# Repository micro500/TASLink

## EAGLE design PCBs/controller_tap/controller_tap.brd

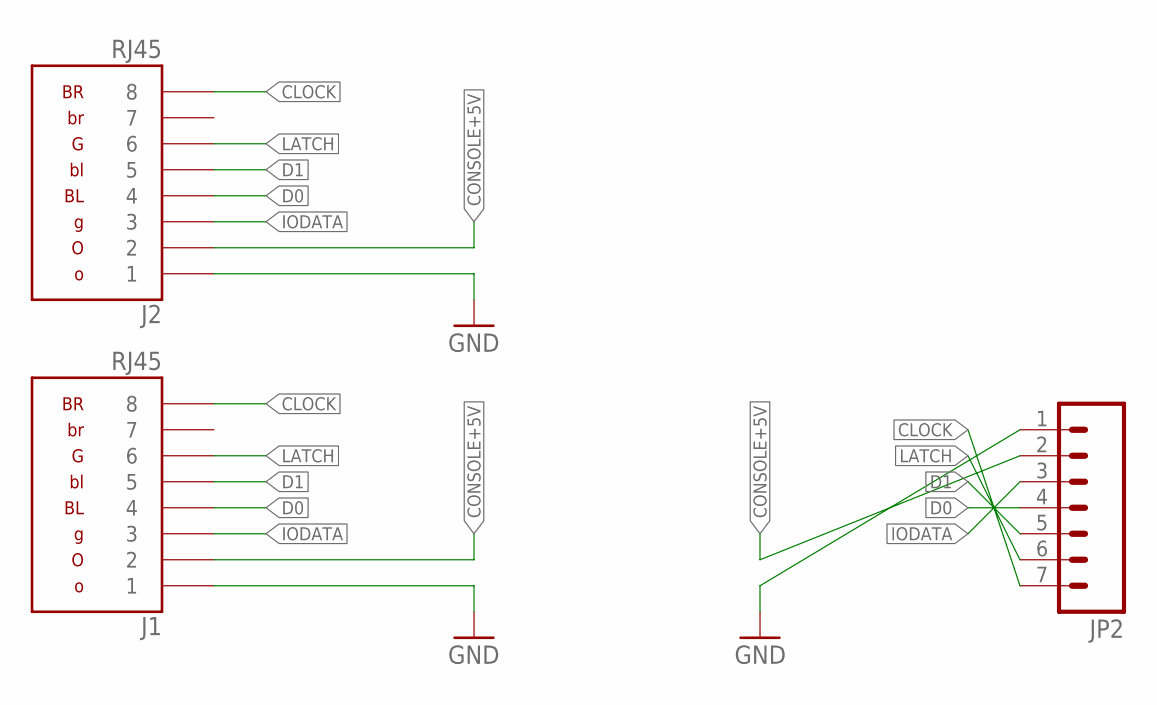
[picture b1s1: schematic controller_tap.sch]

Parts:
J1, J2: RJ45
JP2: M07; 1X07

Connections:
CLOCK: J1.8, J2.8, JP2.7
CONSOLE+5V: J1.2, J2.2, JP2.2
D0: J1.4, J2.4, JP2.4
D1: J1.5, J2.5, JP2.5
GND: J1.1, J2.1, JP2.1
IODATA: J1.3, J2.3, JP2.3
LATCH: J1.6, J2.6, JP2.6

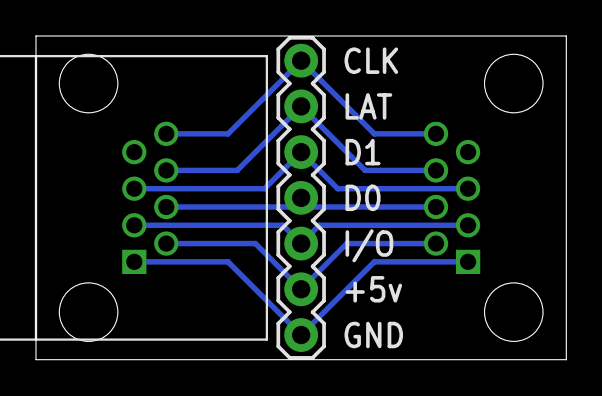
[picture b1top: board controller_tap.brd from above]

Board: 2 copper layers, 29.5 x 18.0 mm, 3 parts (1 on the bottom side), 7 nets.

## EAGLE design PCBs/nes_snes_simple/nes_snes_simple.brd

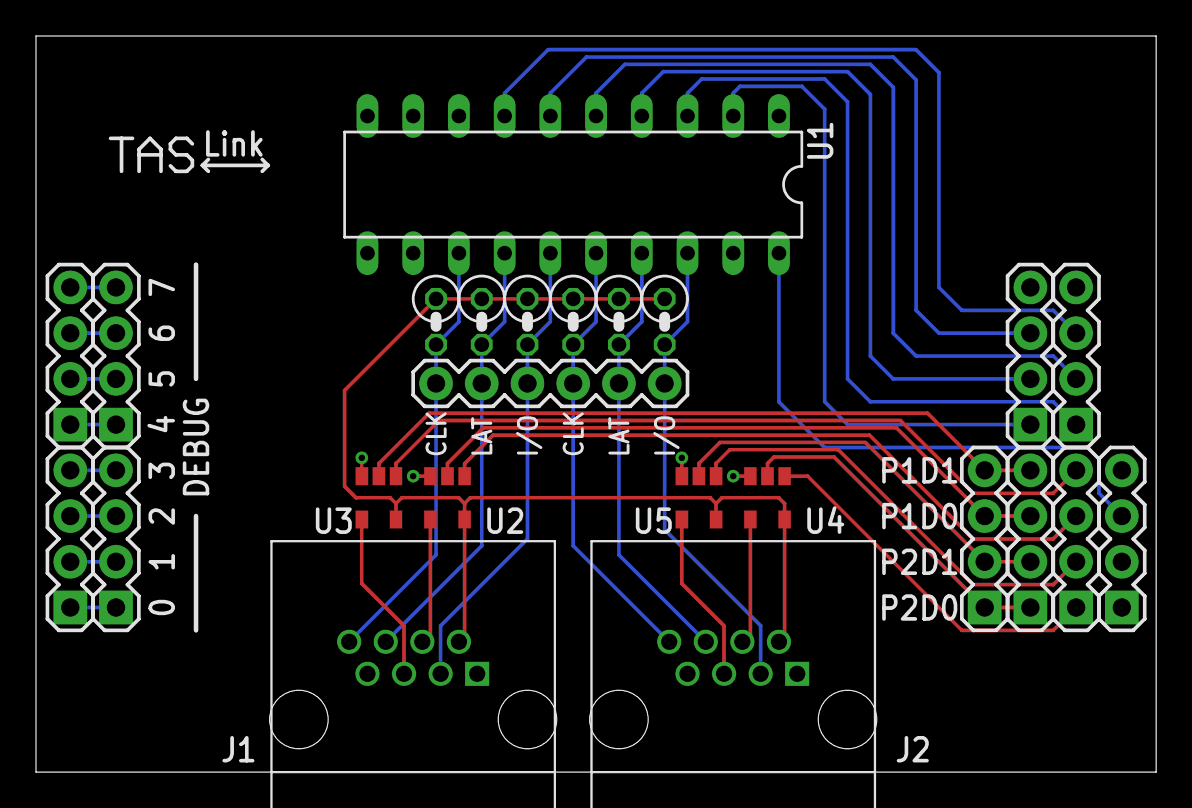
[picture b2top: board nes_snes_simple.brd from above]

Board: 2 copper layers, 62.2 x 40.9 mm, 24 parts (0 on the bottom side), 35 nets.

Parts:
J1, J2: RJ45
JP1, JP2, JP3, JP4, JP7, JP8, JP9, JP10, JP11, JP12: 1X04
JP5: 1X06
R1, R2, R3, R4, R5, R6: 3.6k; 0207/2V
U1: 74245; DIL20
U2, U3, U4, U5: MC74VHC1GT125; TSOP-5

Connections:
+3V3: JP1.3, U1.20
CONSOLE+5V: J1.2, J2.2, R1.1, R2.1, R3.1, R4.1, R5.1, R6.1, U2.P$5, U3.P$5, U4.P$5, U5.P$5
DEBUG0: JP2.4, JP9.4
DEBUG1: JP2.3, JP9.3
DEBUG2: JP2.2, JP9.2
DEBUG3: JP2.1, JP9.1
DEBUG4: JP3.4, JP10.4
DEBUG5: JP3.3, JP10.3
DEBUG6: JP3.2, JP10.2
DEBUG7: JP3.1, JP10.1
GND: J1.1, J2.1, JP1.1, U1.1, U1.10, U1.11, U1.12, U1.19, U2.P$3, U3.P$3, U4.P$3, U5.P$3
P1_CLOCK: J1.8, JP5.1, R1.2, U1.13
P1_CLOCK_LV: JP4.3, U1.7
P1_D0: J1.4, U2.P$4
P1_D0_LV: JP8.3, JP12.3, U2.P$2
P1_D0_OE_LV: JP11.3, U2.P$1
P1_D1: J1.5, U3.P$4
P1_D1_LV: JP8.4, JP12.4, U3.P$2
P1_D1_OE_LV: JP11.4, U3.P$1
P1_IODATA: J1.3, JP5.3, R5.2, U1.15
P1_IODATA_LV: JP4.2, U1.5
P1_LATCH: J1.6, JP5.2, R3.2, U1.14
P1_LATCH_LV: JP7.3, U1.6
P2_CLOCK: J2.8, JP5.4, R2.2, U1.16
P2_CLOCK_LV: JP7.2, U1.4
P2_D0: J2.4, U4.P$4
P2_D0_OE_LV: JP11.1, U4.P$1
P2_D1: J2.5, U5.P$4
P2_D1_LV: JP8.2, JP12.2, U5.P$2
P2_D1_OE_LV: JP11.2, U5.P$1
P2_DO_LV: JP8.1, JP12.1, U4.P$2
P2_IODATA: J2.3, JP5.6, R6.2, U1.18
P2_IODATA_LV: JP7.1, U1.2
P2_LATCH: J2.6, JP5.5, R4.2, U1.17
P2_LATCH_LV: JP4.1, U1.3

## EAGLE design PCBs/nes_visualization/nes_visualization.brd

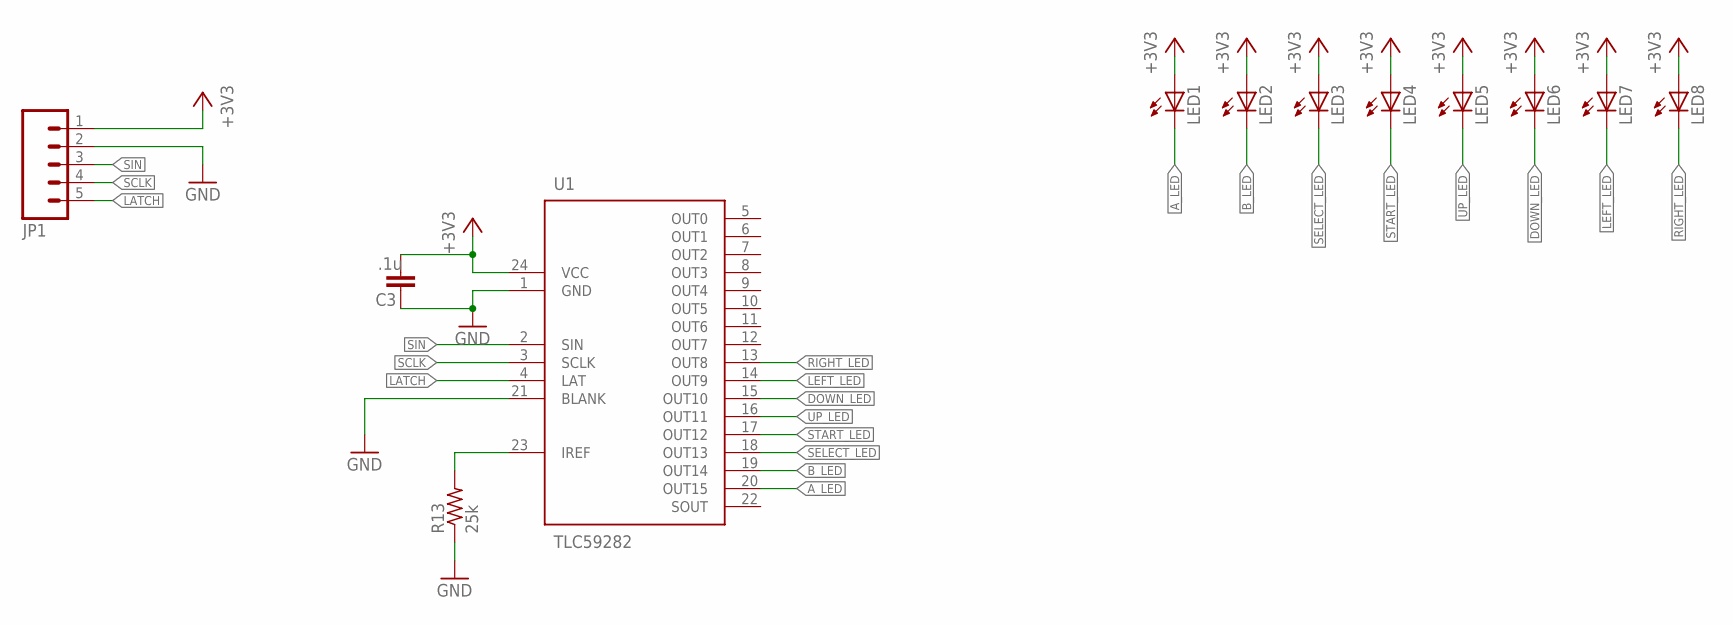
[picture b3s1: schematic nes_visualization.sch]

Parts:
C3: .1u; C0603; MOUSER# 80-C0603C104K5R
JP1: M05PTH; 1X05
LED1, LED2, LED5, LED6, LED7, LED8: LED5MM
LED3, LED4: LED3MM
R13: 25k; R0805
U1: TLC59282; R-PDSO-G24

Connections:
+3V3: C3.1, JP1.1, LED1.A, LED2.A, LED3.A, LED4.A, LED5.A, LED6.A, LED7.A, LED8.A, U1.24 (VCC)
A_LED: LED1.K (C), U1.20 (OUT15)
B_LED: LED2.K (C), U1.19 (OUT14)
DOWN_LED: LED6.K (C), U1.15 (OUT10)
GND: C3.2, JP1.2, R13.1, U1.1 (GND), U1.21 (BLANK)
LATCH: JP1.5, U1.4 (LAT)
LEFT_LED: LED7.K (C), U1.14 (OUT9)
unnamed: R13.2, U1.23 (IREF)
RIGHT_LED: LED8.K (C), U1.13 (OUT8)
SCLK: JP1.4, U1.3 (SCLK)
SELECT_LED: LED3.K (C), U1.18 (OUT13)
SIN: JP1.3, U1.2 (SIN)
START_LED: LED4.K (C), U1.17 (OUT12)
UP_LED: LED5.K (C), U1.16 (OUT11)

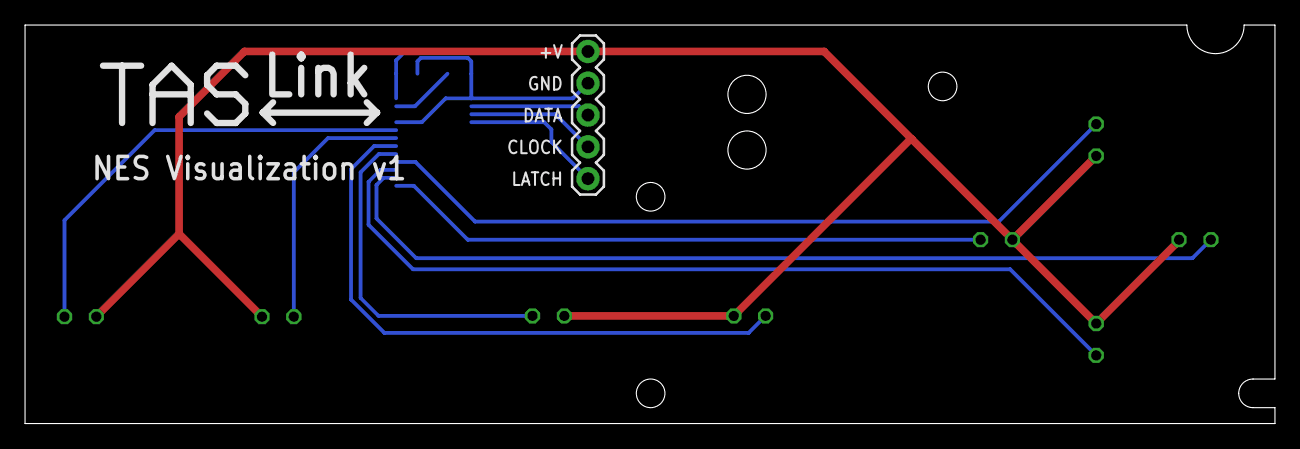
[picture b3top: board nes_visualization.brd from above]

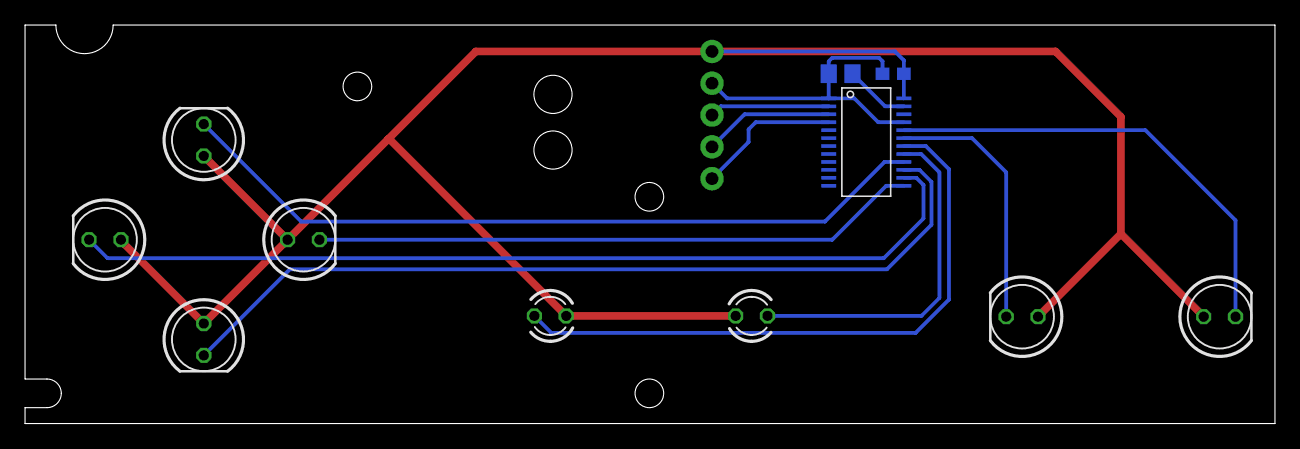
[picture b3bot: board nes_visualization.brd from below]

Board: 2 copper layers, 99.8 x 31.8 mm, 12 parts (11 on the bottom side), 14 nets.

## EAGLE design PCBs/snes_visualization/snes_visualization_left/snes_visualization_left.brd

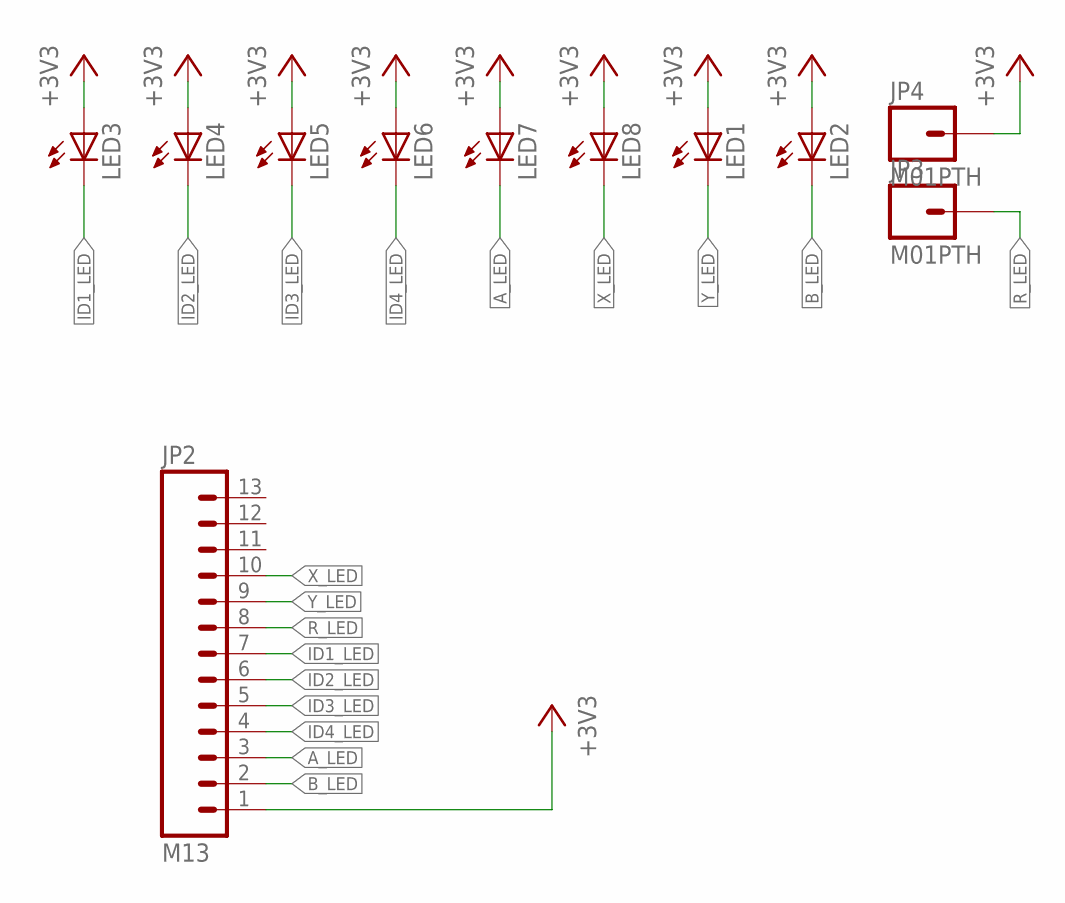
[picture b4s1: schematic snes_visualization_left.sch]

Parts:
JP2: M13; 1X13
JP3, JP4: M01PTH; 1X01
LED1, LED2, LED3, LED4, LED5, LED6, LED7, LED8: LED5MM

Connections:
+3V3: JP2.1, JP4.1, LED1.A, LED2.A, LED3.A, LED4.A, LED5.A, LED6.A, LED7.A, LED8.A
A_LED: JP2.3, LED7.K (C)
B_LED: JP2.2, LED2.K (C)
ID1_LED: JP2.7, LED3.K (C)
ID2_LED: JP2.6, LED4.K (C)
ID3_LED: JP2.5, LED5.K (C)
ID4_LED: JP2.4, LED6.K (C)
R_LED: JP2.8, JP3.1
X_LED: JP2.10, LED8.K (C)
Y_LED: JP2.9, LED1.K (C)

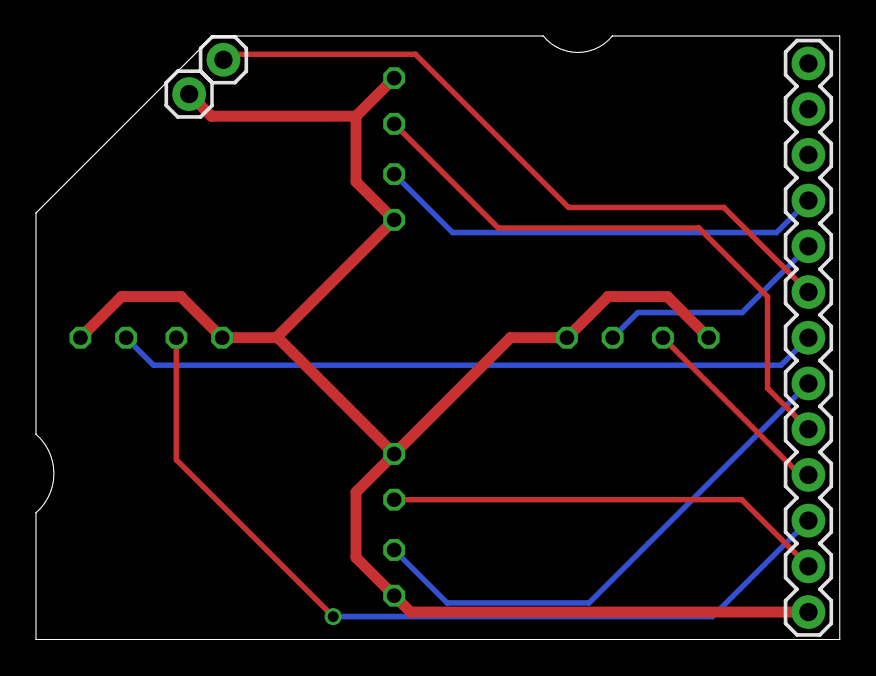
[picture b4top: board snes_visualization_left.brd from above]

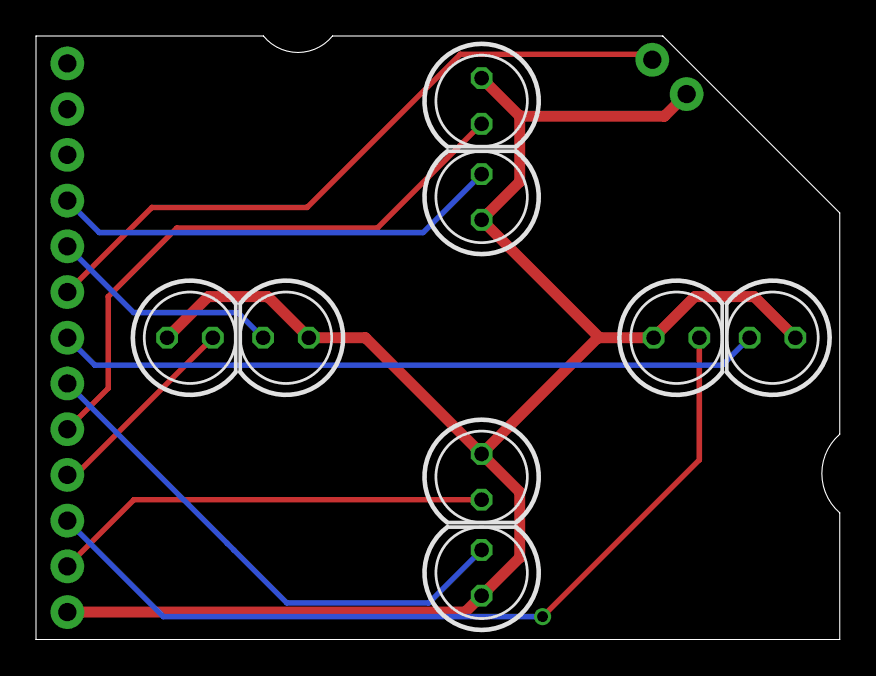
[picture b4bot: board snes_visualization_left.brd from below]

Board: 2 copper layers, 44.7 x 33.5 mm, 11 parts (8 on the bottom side), 10 nets.

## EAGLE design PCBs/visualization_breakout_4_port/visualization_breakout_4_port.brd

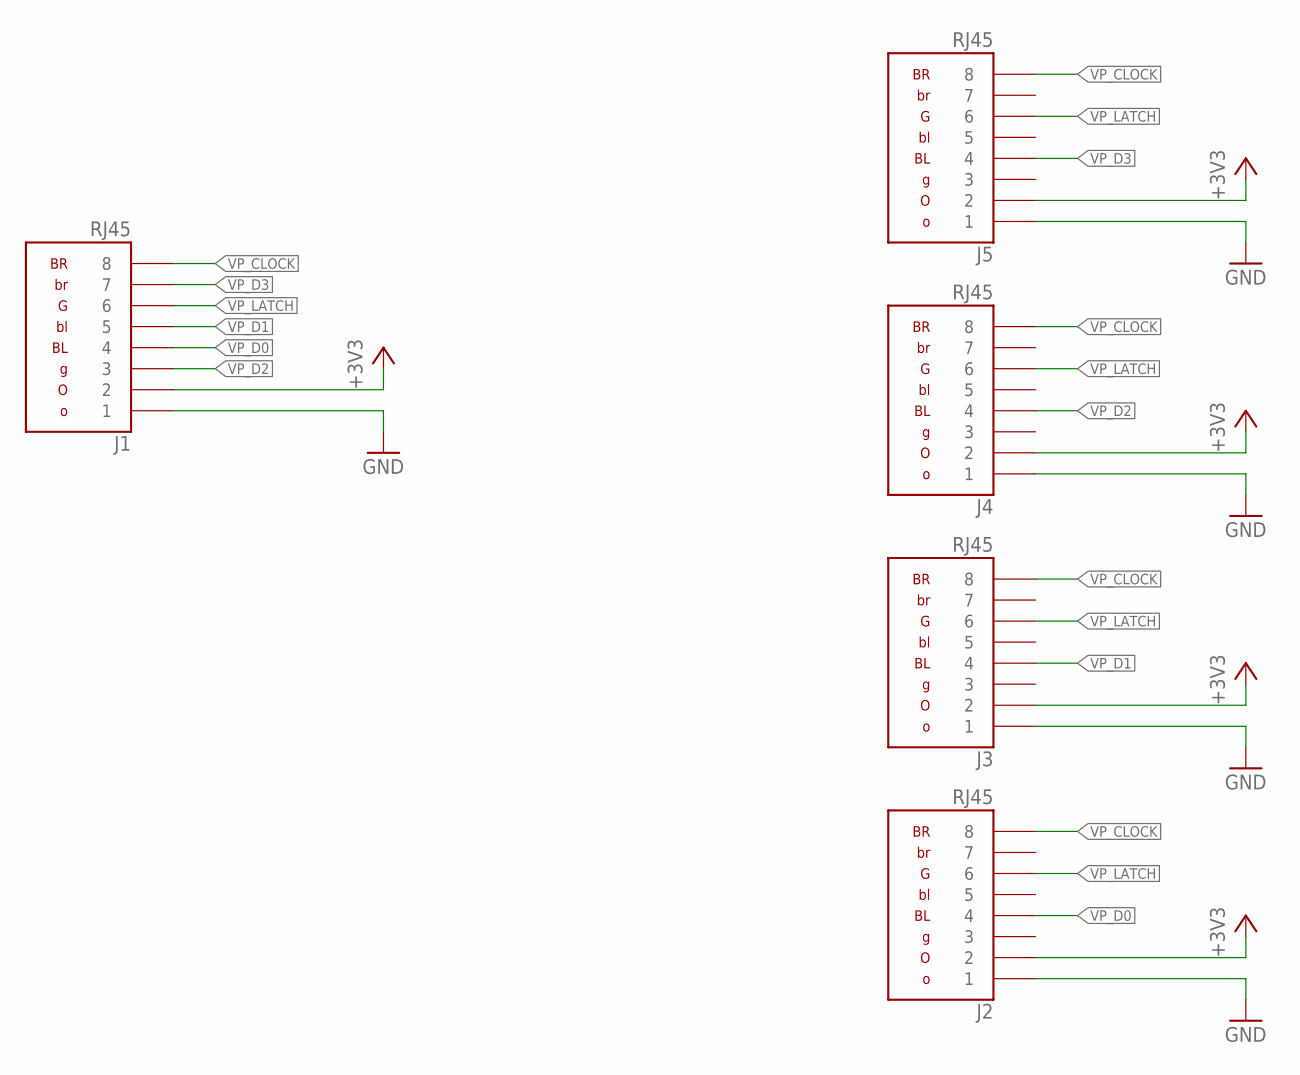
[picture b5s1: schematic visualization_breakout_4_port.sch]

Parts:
J1, J2, J3, J4, J5: RJ45

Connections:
+3V3: J1.2, J2.2, J3.2, J4.2, J5.2
GND: J1.1, J2.1, J3.1, J4.1, J5.1
VP_CLOCK: J1.8, J2.8, J3.8, J4.8, J5.8
VP_D0: J1.4, J2.4
VP_D1: J1.5, J3.4
VP_D2: J1.3, J4.4
VP_D3: J1.7, J5.4
VP_LATCH: J1.6, J2.6, J3.6, J4.6, J5.6

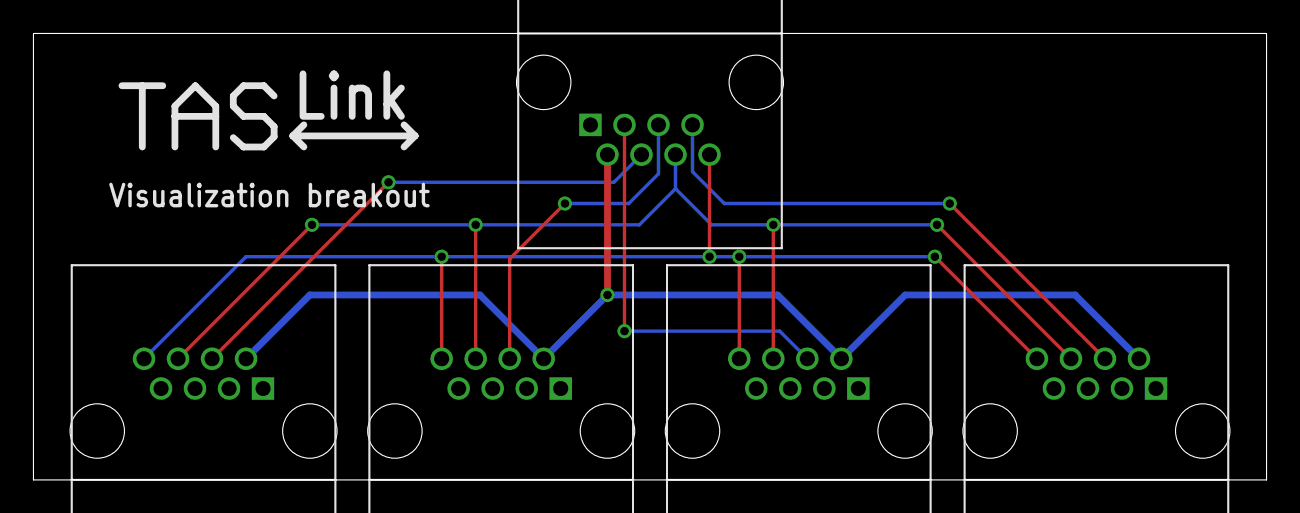
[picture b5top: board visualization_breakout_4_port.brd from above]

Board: 2 copper layers, 73.7 x 26.7 mm, 5 parts (0 on the bottom side), 8 nets.

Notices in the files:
parts and their libraries:
SparkFun-Connectors: Licensing: CC v3.0 Share-Alike You are welcome to use this library for commercial purposes.
